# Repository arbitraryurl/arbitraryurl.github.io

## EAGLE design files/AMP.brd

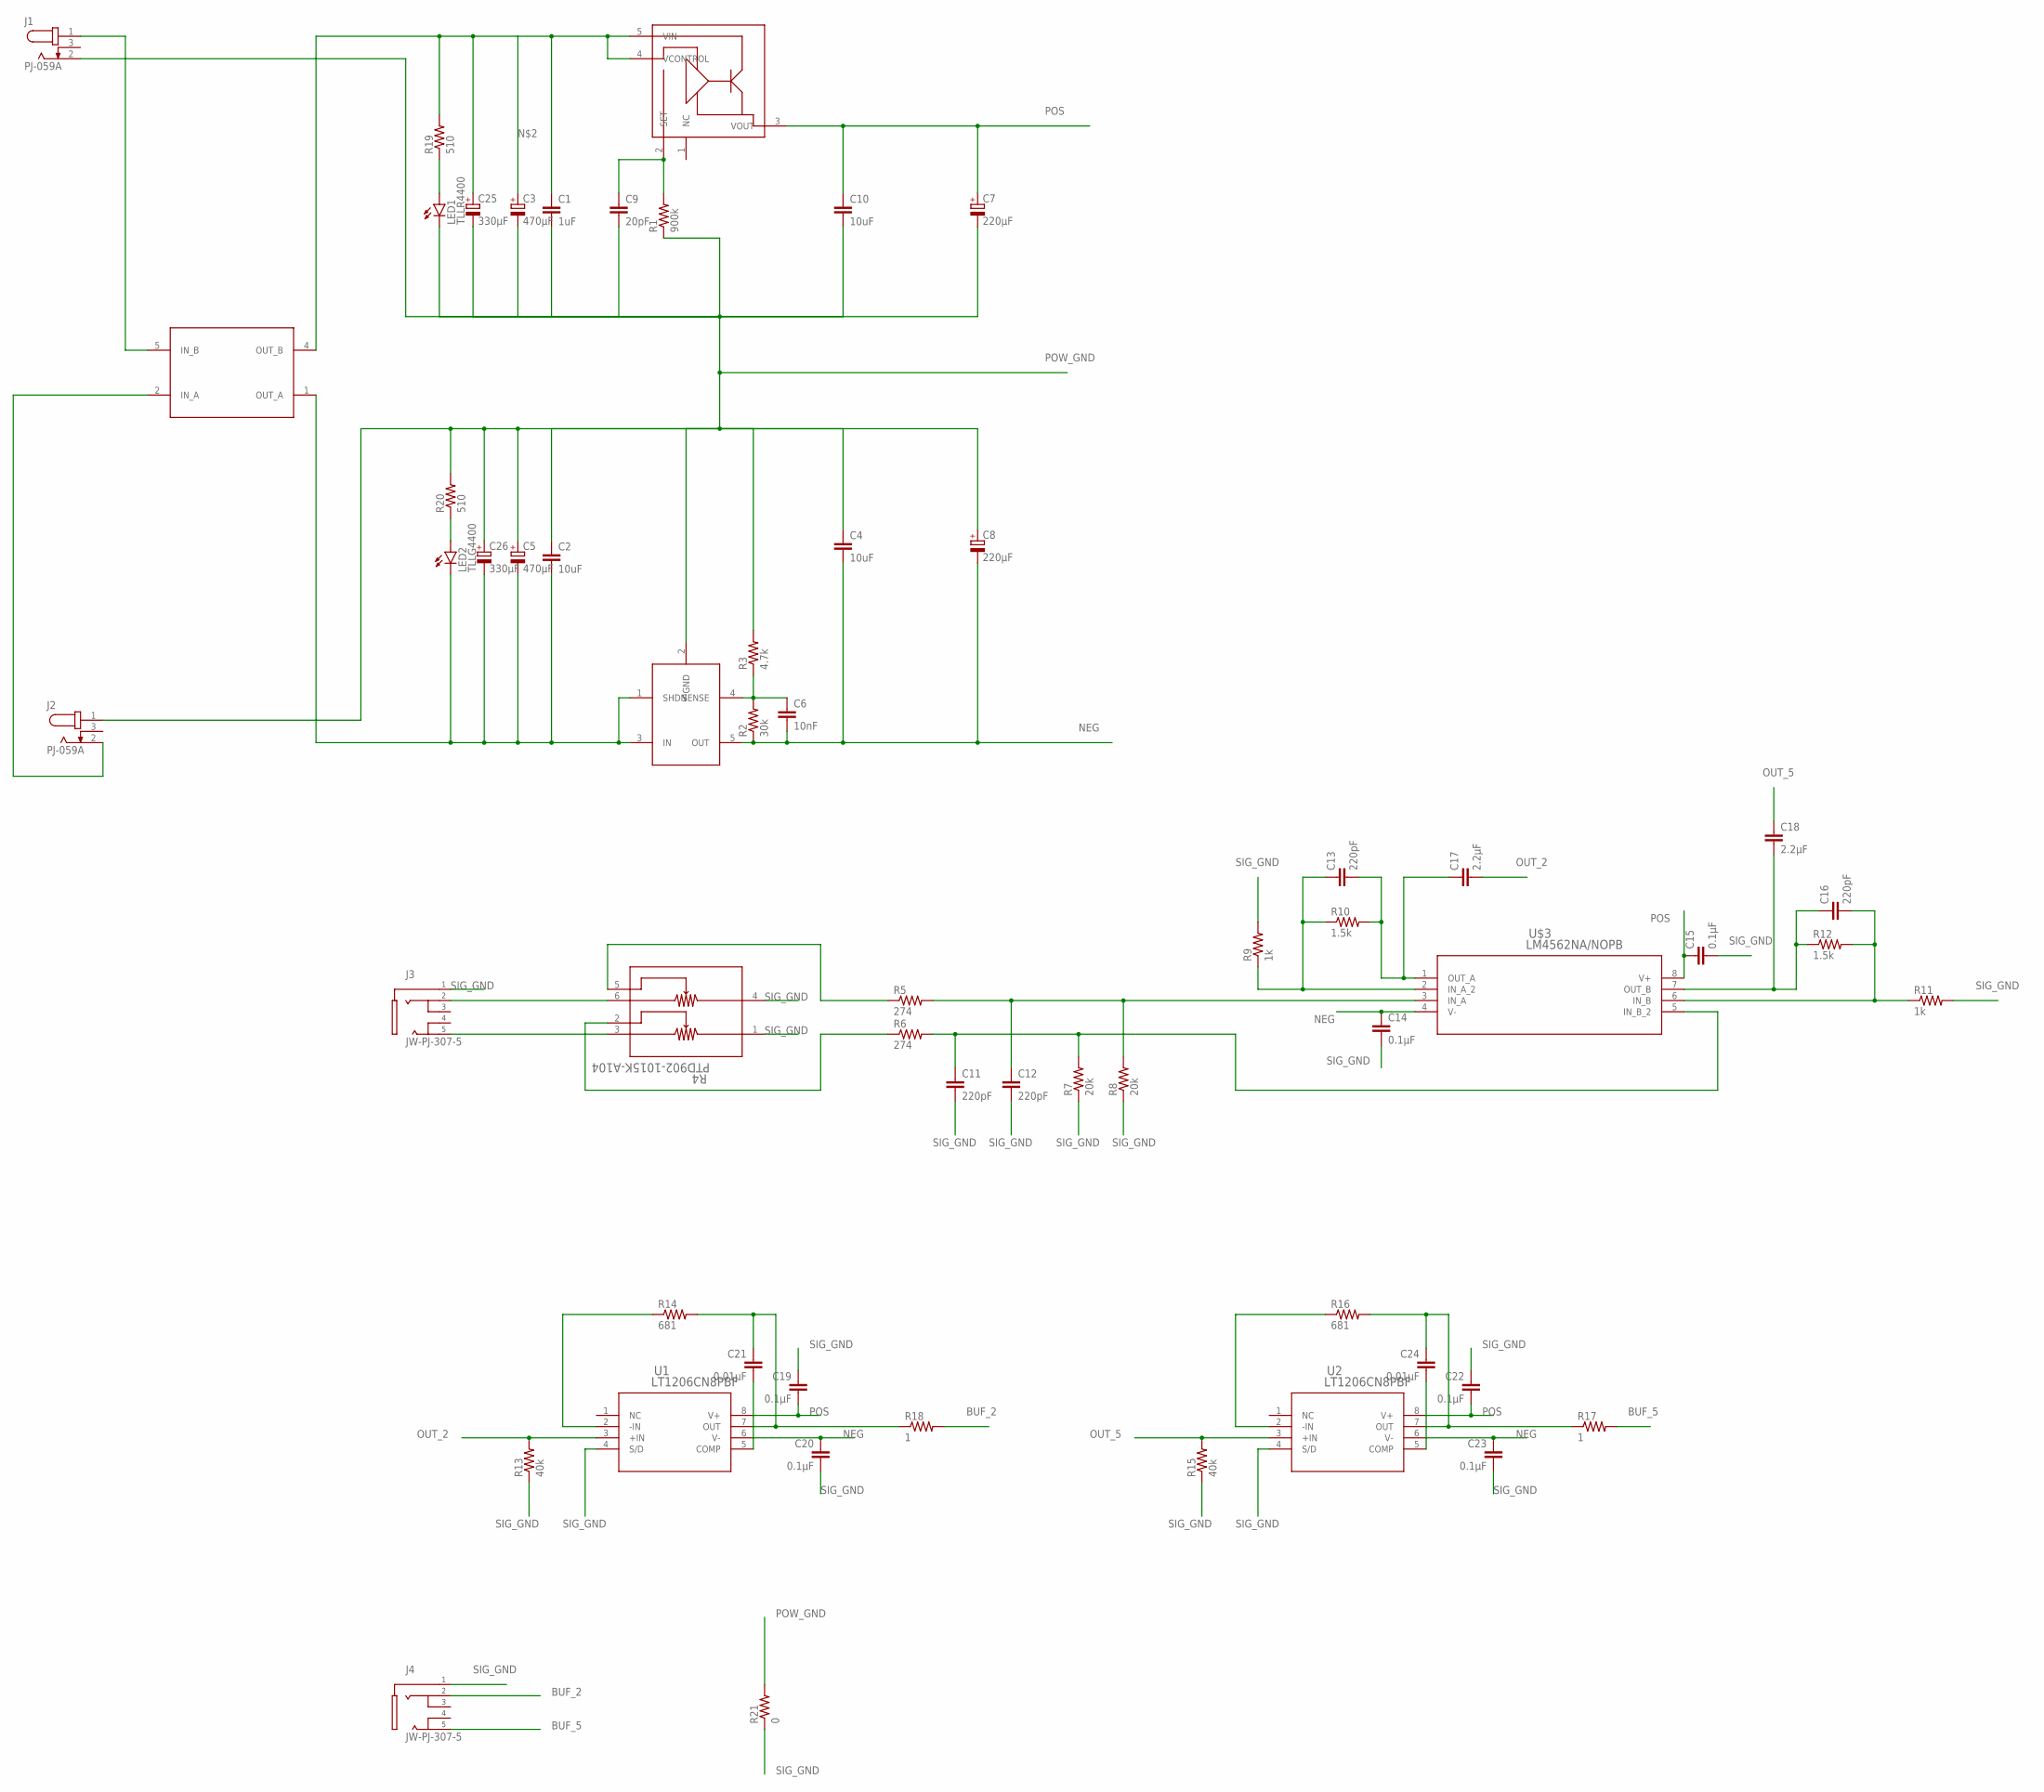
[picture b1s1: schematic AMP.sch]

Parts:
C1: 1uF; C050-025X075
C2, C4, C10: 10uF; C050-025X075
C3, C5: 470µF; E3,5-8
C6: 10nF; C025-025X050
C7, C8: 220µF; E3,5-8
C9: 20pF; C025-025X050
C11, C12, C13, C16: 220pF; C050-025X075
C14, C15, C19, C20, C22, C23: 0.1µF; C050-025X075
C17, C18: 2.2µF; C050-025X075
C21, C24: 0.01µF; C050-025X075
C25, C26: 330µF; E3,5-8
J1, J2: PJ-059A; CUI_PJ-059A
J3, J4: JW-PJ-307-5; JW-PJ-307-X
LED1: TLLR4400; LED3MM
LED2: TLLG4400; LED3MM
R1: 900k; 0207/10
R2: 30k; 0207/10
R3: 4.7k; 0207/10
R4: PTD902-1015K-A104; PTD902-15K_BRN
R5, R6: 274; 0207/10
R7, R8: 20k; 0207/10
R9, R11: 1k; 0207/10
R10, R12: 1.5k; 0207/10
R13, R15: 40k; 0207/10
R14, R16: 681; 0207/10
R17, R18: 1; 0207/10
R19, R20: 510; 0207/10
R21: 0; 0207/10
SWITCH1: M2022
U1, U2: LT1206CN8PBF; PDIP-8_N_LIT
U$1: LT3080; TO220-5
U$2: LT3015LT3015; TO220-5
U$3: LM4562NA/NOPB; N08E

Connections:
BUF_2: J4.P$2 (2), R18.2
BUF_5: J4.P$4 (5), R17.2
unnamed: R4.5, R5.1
unnamed: C1.1, C3.+, C25.+, R19.2, SWITCH1.4 (OUT_B), U$1.4 (VCONTROL), U$1.5 (VIN)
unnamed: C9.1, R1.2, U$1.2 (SET)
unnamed: R4.2, R6.1
unnamed: C2.2, C5.-, C26.-, LED2.K (C), SWITCH1.1 (OUT_A), U$2.1 (SHDN), U$2.3 (IN)
unnamed: J3.P$2 (2), R4.6
unnamed: C6.1, R2.2, R3.1, U$2.4 (SENSE)
unnamed: J3.P$4 (5), R4.3
unnamed: C12.1, R5.2, R8.2, U$3.3 (IN_A)
unnamed: C11.1, R6.2, R7.2, U$3.5 (IN_B_2)
unnamed: C16.2, R11.1, R12.2, U$3.6 (IN_B)
unnamed: C13.2, C17.1, R10.2, U$3.1 (OUT_A)
unnamed: C21.1, R14.2, R18.1, U1.7 (OUT)
unnamed: C13.1, R9.1, R10.1, U$3.2 (IN_A_2)
unnamed: C16.1, C18.2, R12.1, U$3.7 (OUT_B)
unnamed: R14.1, U1.2 (-IN)
unnamed: C21.2, U1.5 (COMP)
unnamed: C24.1, R16.2, R17.1, U2.7 (OUT)
unnamed: R16.1, U2.2 (-IN)
unnamed: C24.2, U2.5 (COMP)
unnamed: J2.2, SWITCH1.2 (IN_A)
unnamed: J1.1, SWITCH1.5 (IN_B)
unnamed: LED1.A, R19.1
unnamed: LED2.A, R20.1
NEG: C4.2, C6.2, C8.-, C14.1, C20.1, C23.1, R2.1, U1.6 (V-), U2.6 (V-), U$2.5 (OUT), U$3.4 (V-)
OUT_2: C17.2, R13.2, U1.3 (+IN)
OUT_5: C18.1, R15.2, U2.3 (+IN)
POS: C7.+, C10.1, C15.1, C19.2, C22.2, U1.8 (V+), U2.8 (V+), U$1.3 (VOUT), U$3.8 (V+)
POW_GND: C1.2, C2.1, C3.-, C4.1, C5.+, C7.-, C8.+, C9.2, C10.2, C25.-, C26.+, J1.2, J2.1, LED1.K (C), R1.1, R3.2, R20.2, R21.2, U$2.2 (GND)
SIG_GND: C11.2, C12.2, C14.2, C15.2, C19.1, C20.2, C22.1, C23.2, J3.P$5 (1), J4.P$5 (1), R4.1, R4.4, R7.1, R8.1, R9.2, R11.2, R13.1, R15.1, R21.1, U1.4 (S/D), U2.4 (S/D)

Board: 2 copper layers, 59 parts (1 on the bottom side), 32 nets, no tracks yet.

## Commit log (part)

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2020-11-15 Added my project
2022-04-19 Create CNAME
2022-04-28 2022 update
2022-04-28 fixed js
2022-04-28 typo
2022-05-01 update 2
2022-05-01 Reupload
2022-05-01 mobile updates
2022-05-01 word
2022-05-01 video width
2022-05-05 Removed photo catageory
2022-05-05 files
2022-05-06 favicon
2022-05-06 favicon2
2022-05-07 Added voc info
2022-05-13 image edits
2022-05-22 blinker added
2023-06-04 location
2024-02-21 Reduce a bit
2024-11-02 2024 Website Overhaul (website v2)
2024-11-02 Test
2024-11-03 Added thumbnails
2024-11-03 Resized images
2024-11-03 Update text
2024-11-03 Added icon
2025-01-09 Changes
    About page, added padding on mobile
2025-01-09 Index Padding Bottom

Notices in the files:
parts and their libraries:
COPYRIGHT: Copyright (C) 2018 Accelerated Designs. All rights reserved
